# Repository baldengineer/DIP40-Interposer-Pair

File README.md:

## DIP40 Interposer Board Pair
This adapter makes it easier to probe a DIP-40 (0.6" wide) chip using a logic analyzer or mixed-signal oscilloscope. The boards breakout each of the signals.

Originally this was designed to test the Z80 and ULA chips of a ZX-81. However, there is nothing chip-specific in this design.

Currently, the boards are untested and being manufactured.

## PCB-Side Board
This board plugs into the PCB or the socket on the PCB. It should have a 02x20 pin-socket in the middle facing "up". Two pin-headers go near the outside edges.

The rendered image shows right-angle and straight connectors. It is not clear yet which is a better option. Consider how your probes connect to the pins.

## Chip Carrier Board
The chip under test plugs into this board. Ideally, you probably want to use a socket to connect a 0.6" wide DIP-40 chip. Right-angled pin-headers allow for a clean mating. If you use "straight" header-pins, half of the logic probe pins are blocked.

## Bald Engineer on Twitch
This board was designed, built, and tested live with the Bald Engineer. Check out his electronics live stream at: [https://twitch.tv/baldengineer](https://twitch.tv/baldengineer).

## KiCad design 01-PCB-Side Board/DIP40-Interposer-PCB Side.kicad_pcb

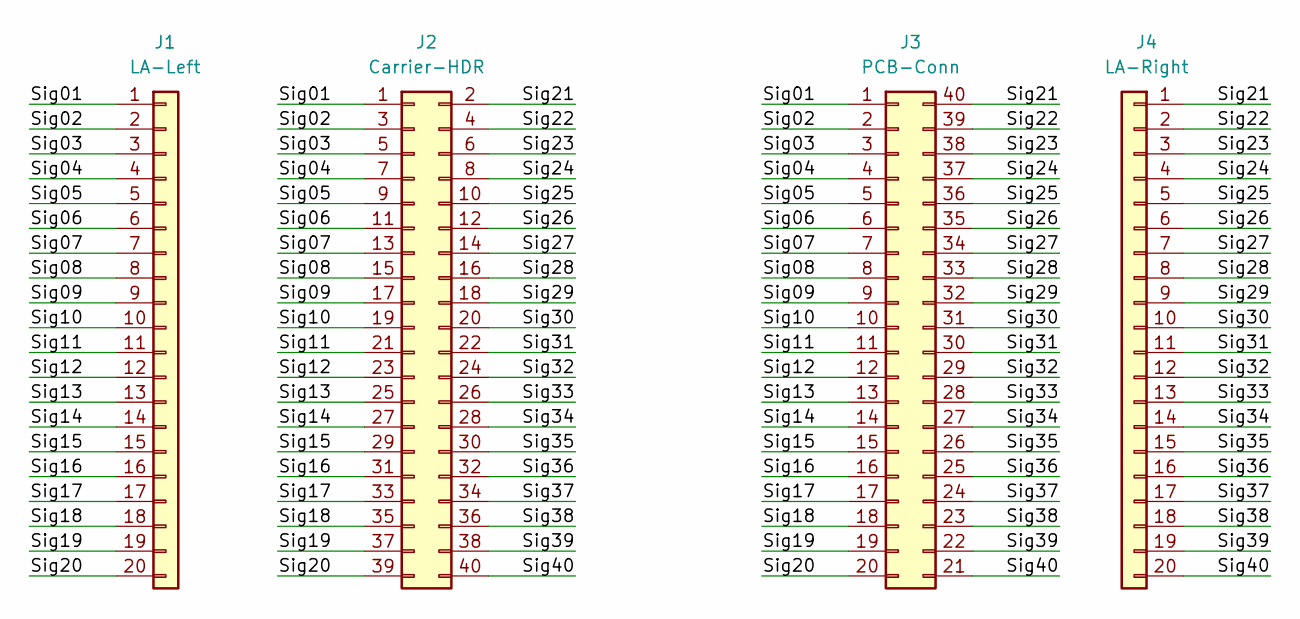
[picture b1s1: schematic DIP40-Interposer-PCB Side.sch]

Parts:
J1: LA-Left; PinHeader_1x20_P2.54mm_Vertical
J2: Carrier-HDR; PinSocket_2x20_P2.54mm_Vertical
J3: PCB-Conn; DIP-40_W25.4mm_Socket_LongPads
J4: LA-Right; PinHeader_1x20_P2.54mm_Vertical

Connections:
/Sig01: J1.1, J2.1, J3.1
/Sig02: J1.2, J2.3, J3.2
/Sig03: J1.3, J2.5, J3.3
/Sig04: J1.4, J2.7, J3.4
/Sig05: J1.5, J2.9, J3.5
/Sig06: J1.6, J2.11, J3.6
/Sig07: J1.7, J2.13, J3.7
/Sig08: J1.8, J2.15, J3.8
/Sig09: J1.9, J2.17, J3.9
/Sig10: J1.10, J2.19, J3.10
/Sig11: J1.11, J2.21, J3.11
/Sig12: J1.12, J2.23, J3.12
/Sig13: J1.13, J2.25, J3.13
/Sig14: J1.14, J2.27, J3.14
/Sig15: J1.15, J2.29, J3.15
/Sig16: J1.16, J2.31, J3.16
/Sig17: J1.17, J2.33, J3.17
/Sig18: J1.18, J2.35, J3.18
/Sig19: J1.19, J2.37, J3.19
/Sig20: J1.20, J2.39, J3.20
/Sig21: J2.2, J3.40, J4.1
/Sig22: J2.4, J3.39, J4.2
/Sig23: J2.6, J3.38, J4.3
/Sig24: J2.8, J3.37, J4.4
/Sig25: J2.10, J3.36, J4.5
/Sig26: J2.12, J3.35, J4.6
/Sig27: J2.14, J3.34, J4.7
/Sig28: J2.16, J3.33, J4.8
/Sig29: J2.18, J3.32, J4.9
/Sig30: J2.20, J3.31, J4.10
/Sig31: J2.22, J3.30, J4.11
/Sig32: J2.24, J3.29, J4.12
/Sig33: J2.26, J3.28, J4.13
/Sig34: J2.28, J3.27, J4.14
/Sig35: J2.30, J3.26, J4.15
/Sig36: J2.32, J3.25, J4.16
/Sig37: J2.34, J3.24, J4.17
/Sig38: J2.36, J3.23, J4.18
/Sig39: J2.38, J3.22, J4.19
/Sig40: J2.40, J3.21, J4.20

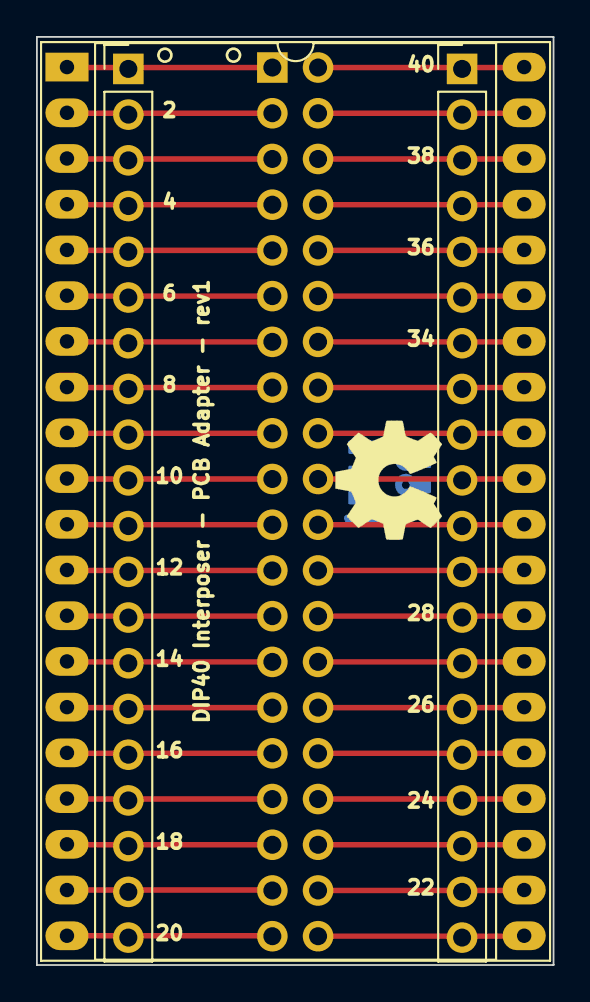
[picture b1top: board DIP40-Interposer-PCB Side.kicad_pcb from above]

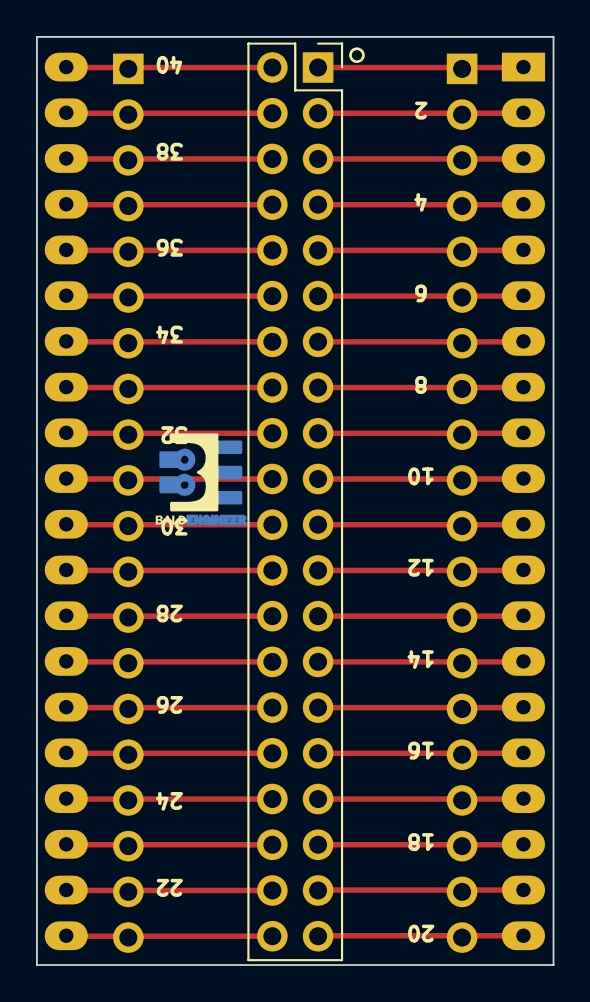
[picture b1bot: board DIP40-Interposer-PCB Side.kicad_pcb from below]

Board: 2 copper layers, 28.7 x 51.6 mm, 5 parts (2 on the bottom side), 40 nets.

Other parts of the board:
svg2mod: G***; BE5

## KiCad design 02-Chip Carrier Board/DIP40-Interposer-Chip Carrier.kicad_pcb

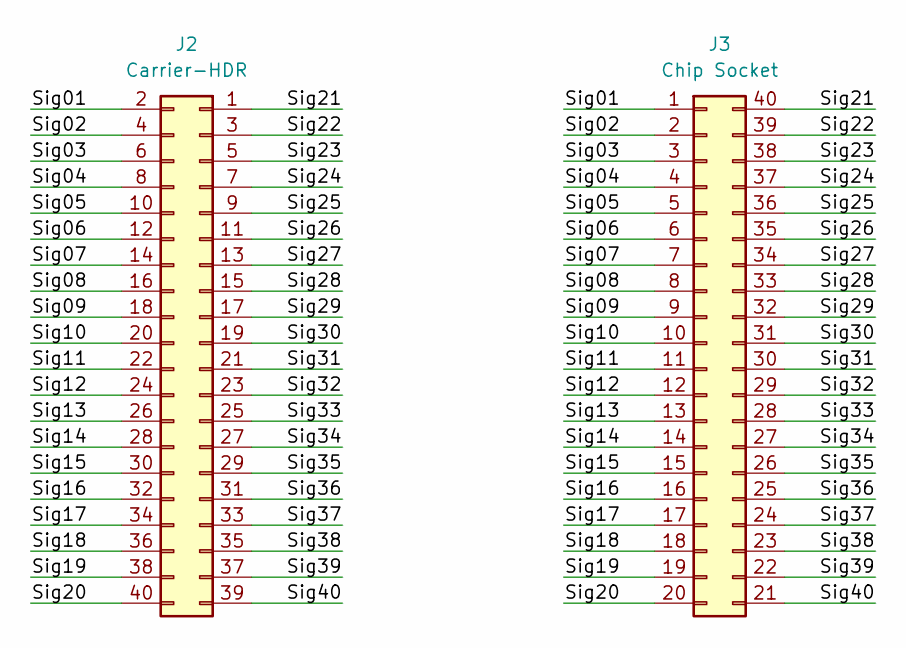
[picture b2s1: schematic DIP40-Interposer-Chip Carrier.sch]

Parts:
J2: Carrier-HDR; PinHeader_2x20_P2.54mm_Horizontal
J3: Chip Socket; DIP-40_W25.4mm_Socket_LongPads

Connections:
/Sig01: J2.2, J3.1
/Sig02: J2.4, J3.2
/Sig03: J2.6, J3.3
/Sig04: J2.8, J3.4
/Sig05: J2.10, J3.5
/Sig06: J2.12, J3.6
/Sig07: J2.14, J3.7
/Sig08: J2.16, J3.8
/Sig09: J2.18, J3.9
/Sig10: J2.20, J3.10
/Sig11: J2.22, J3.11
/Sig12: J2.24, J3.12
/Sig13: J2.26, J3.13
/Sig14: J2.28, J3.14
/Sig15: J2.30, J3.15
/Sig16: J2.32, J3.16
/Sig17: J2.34, J3.17
/Sig18: J2.36, J3.18
/Sig19: J2.38, J3.19
/Sig20: J2.40, J3.20
/Sig21: J2.1, J3.40
/Sig22: J2.3, J3.39
/Sig23: J2.5, J3.38
/Sig24: J2.7, J3.37
/Sig25: J2.9, J3.36
/Sig26: J2.11, J3.35
/Sig27: J2.13, J3.34
/Sig28: J2.15, J3.33
/Sig29: J2.17, J3.32
/Sig30: J2.19, J3.31
/Sig31: J2.21, J3.30
/Sig32: J2.23, J3.29
/Sig33: J2.25, J3.28
/Sig34: J2.27, J3.27
/Sig35: J2.29, J3.26
/Sig36: J2.31, J3.25
/Sig37: J2.33, J3.24
/Sig38: J2.35, J3.23
/Sig39: J2.37, J3.22
/Sig40: J2.39, J3.21

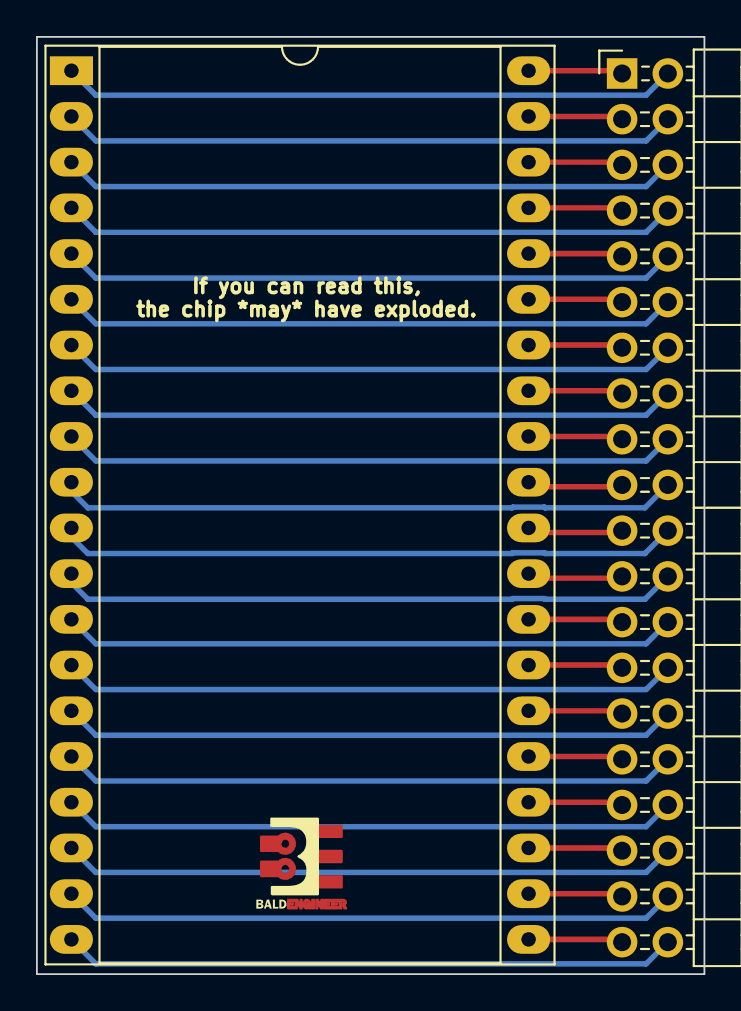
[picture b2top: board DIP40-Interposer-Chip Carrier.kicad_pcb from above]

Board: 2 copper layers, 37.1 x 52.1 mm, 3 parts (0 on the bottom side), 40 nets.

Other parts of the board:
svg2mod: G***; BE5
